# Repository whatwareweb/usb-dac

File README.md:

# usb-dac

USB DAC based on TI PCM2912A IC

This design is tested and working, I use it as my daily driver DAC

## pcb fabrication
I ordered my pcbs from OSHpark, the project link is here for a 1-click order that is already configured and will work well https://oshpark.com/shared_projects/iy0FjLmS

## performance tweaking
This DAC has been designed with good low-frequency response in mind, large output capacitors are used to ensure very low frequencies can be reproduced

To adjust high-frequency response, C4 and C5 can be decreased to allow higher-frequency sounds to make it to the output. Too high of a capacitance for either of these will lead to a muffled sound

C9 and C10 are the output capacitors, the Rubycon model listed in the BOM does very well for the price but they can be swapped out for any higher quality electrolytic capacitor with the same lead spacing. to increase LF response make these a larger value, to decrease make them a smaller value. I just used these as I had like 70 of them spare from another project

## assembly
Check the assembly directory for assembly pictures

This board design is tested and working, but if you would like any help you can open a github issue and I'll try my best (no i will most likely not give you one for free, sorry)

During assembly it is very helpful to open the board view in KiCad to see the component values and the BOM

This board has been designed with easy assembly in mind, there are only 2 SMD parts which you could get assembled for you at a PCB assembly service, the rest of the parts are through-hole and very easy to solder DIY.

## parts
The parts in the BOM can all be purchased at Mouser electronics (DigiKey probably has them too, I didn't check)

I just went with the cheapest option of the rated component value with a minimum voltage rating of 5v, so if you need to get components from some other supplier you can do that as well and it will probably work, just make sure to double-check the lead spacing for the capacitors, inductors, etc

## bom
To export the BOM, open the schematic in Kicad, and click the BOM icon in the toolbar, from there you can copy/paste or export

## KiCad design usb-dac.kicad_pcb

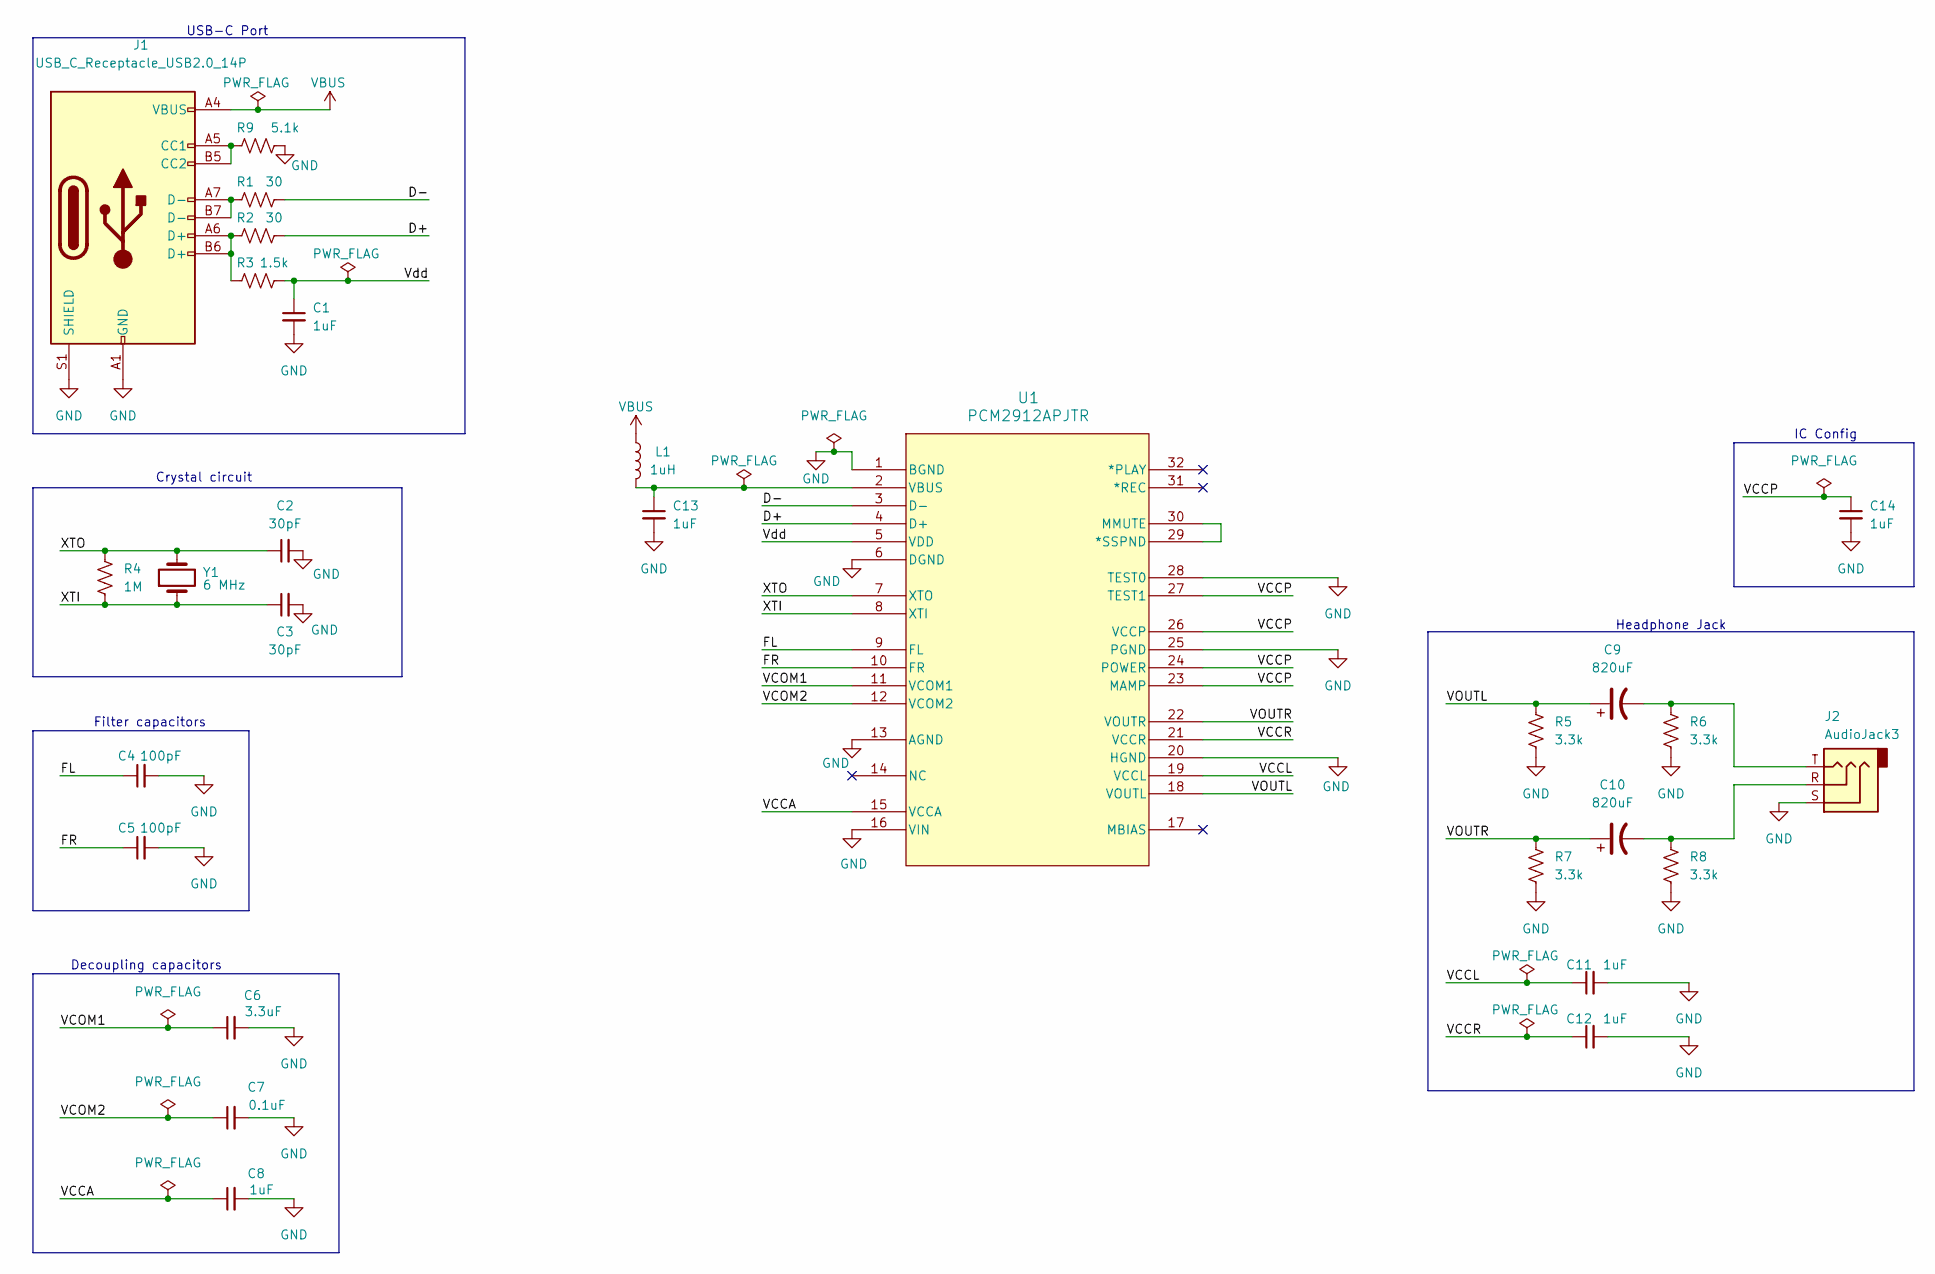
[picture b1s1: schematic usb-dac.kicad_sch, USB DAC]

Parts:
C1, C8, C11, C12, C13, C14: 1uF; C_Rect_L7.0mm_W2.0mm_P5.00mm; Mfr. # FG28X7R1E105KRT00
C2, C3: 30pF; C_Rect_L7.0mm_W2.0mm_P5.00mm; Mfr. # K300J10C0GF5UH5
C4, C5: 100pF; C_Rect_L7.0mm_W2.0mm_P5.00mm; Mfr. # XR501101K040HAND5P
C6: 3.3uF; C_Rect_L7.0mm_W2.0mm_P5.00mm; Mfr. # FA24X7R1E335KRU06
C7: 0.1uF; C_Rect_L7.0mm_W2.0mm_P5.00mm; Mfr. # K104K10X7RF5UH5
C9, C10: 820uF; CP_Radial_D8.0mm_P3.50mm; Mfr. # 6.3ZLH820MEFC8X11.5
J1: USB_C_Receptacle_USB2.0_14P; USB_C_Receptacle_GCT_USB4105-xx-A_16P_TopMnt_Horizontal; Mfr. # USB4085
J2: AudioJack3; Jack_3.5mm_CUI_SJ1-3523N_Horizontal; Mfr. # SJ1-3523N
L1: 1uH; L_Axial_L5.3mm_D2.2mm_P7.62mm_Horizontal_Vishay_IM-1; Mfr. # AICC-02-1R0M-T
R1, R2: 30; R_Axial_DIN0207_L6.3mm_D2.5mm_P10.16mm_Horizontal; Mfr. # CF14JT30R0
R3: 1.5k; R_Axial_DIN0207_L6.3mm_D2.5mm_P10.16mm_Horizontal; Mfr. # CFR-12JB-52-1K5
R4: 1M; R_Axial_DIN0207_L6.3mm_D2.5mm_P10.16mm_Horizontal; Mfr. # RNF18FTD1M00
R5, R6, R7, R8: 3.3k; R_Axial_DIN0207_L6.3mm_D2.5mm_P10.16mm_Horizontal; Mfr. # CFM14JT3K30
R9: 5.1k; R_Axial_DIN0207_L6.3mm_D2.5mm_P10.16mm_Horizontal; Mfr. # CF18JT5K10
U1: PCM2912APJTR; TQFP-32_7x7mm_P0.8mm; Mfr. # PCM2912APJTR
Y1: 6 MHz; Crystal_HC49-U_Vertical; Mfr. # ATS060

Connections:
/D+: R2.2, U1.4 (D+)
/D-: R1.2, U1.3 (D-)
/FL: C4.1, U1.9 (FL)
/FR: C5.1, U1.10 (FR)
/VCCA: C8.1, U1.15 (VCCA)
/VCCL: C11.1, U1.19 (VCCL)
/VCCP: C14.1, U1.23 (MAMP), U1.24 (POWER), U1.26 (VCCP), U1.27 (TEST1)
/VCCR: C12.1, U1.21 (VCCR)
/VCOM1: C6.1, U1.11 (VCOM1)
/VCOM2: C7.1, U1.12 (VCOM2)
/VOUTL: C9.1, R5.1, U1.18 (VOUTL)
/VOUTR: C10.1, R7.1, U1.22 (VOUTR)
/Vdd: C1.1, R3.2, U1.5 (VDD)
/XTI: C3.1, R4.2, U1.8 (XTI), Y1.1
/XTO: C2.1, R4.1, U1.7 (XTO), Y1.2
GND: C1.2, C2.2, C3.2, C4.2, C5.2, C6.2, C7.2, C8.2, C11.2, C12.2, C13.2, C14.2, J1.A1 (GND), J1.A12 (GND), J1.B1 (GND), J1.B12 (GND), J1.S1 (SHIELD), J2.S, R5.2, R6.2, R7.2, R8.2, R9.2, U1.1 (BGND), U1.6 (DGND), U1.13 (AGND), U1.16 (VIN), U1.20 (HGND), U1.25 (PGND), U1.28 (TEST0)
unnamed: C9.2, J2.T, R6.1
unnamed: C10.2, J2.R, R8.1
unnamed: J1.A5 (CC1), J1.B5 (CC2), R9.1
unnamed: J1.A6 (D+), J1.B6 (D+), R2.1, R3.1
unnamed: J1.A7 (D-), J1.B7 (D-), R1.1
unnamed: U1.29 (*SSPND), U1.30 (MMUTE)
unnamed: C13.1, L1.2, U1.2 (VBUS)
VBUS: J1.A4 (VBUS), J1.A9 (VBUS), J1.B4 (VBUS), J1.B9 (VBUS), L1.1

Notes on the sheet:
Filter capacitors
Headphone Jack
USB-C Port
Crystal circuit
Decoupling capacitors
IC Config

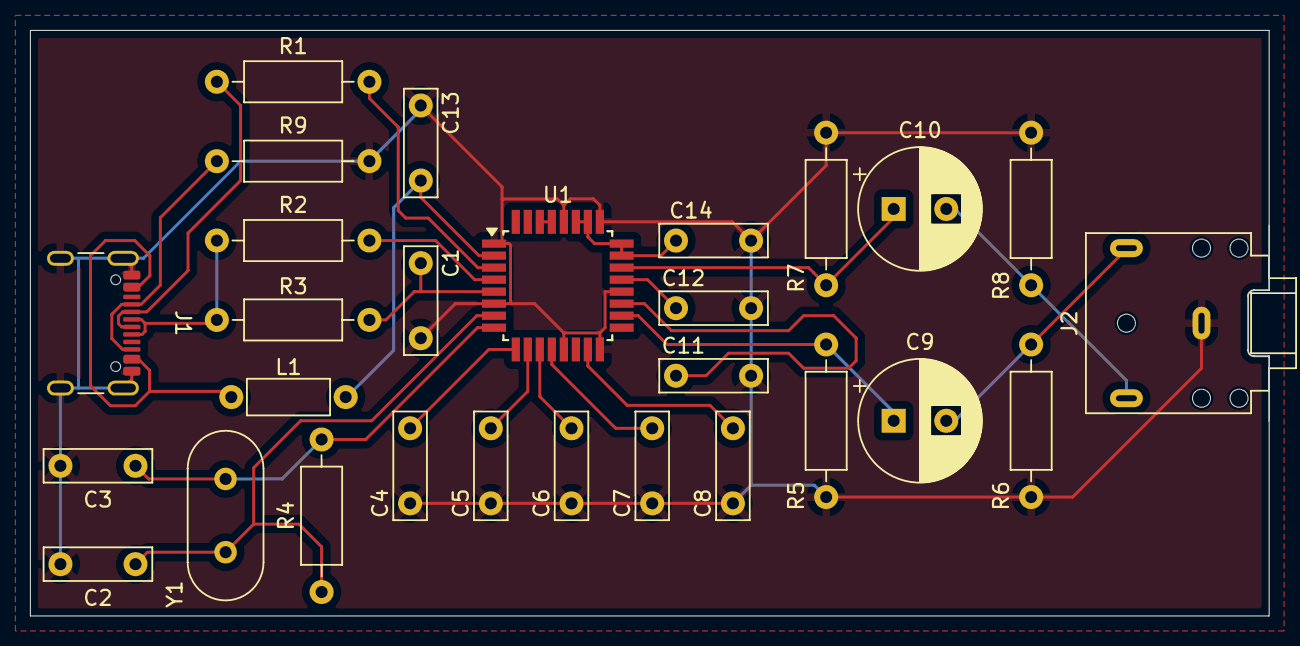
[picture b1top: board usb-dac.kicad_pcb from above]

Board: 2 copper layers, 82.5 x 38.9 mm, 28 parts (0 on the bottom side), 24 nets.

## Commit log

2024-07-12 Add initial libraries and schematics
2024-07-12 Create LICENSE
2024-07-12 Update schematic
2024-07-13 update schematic with new components
2024-07-13 Update schematic with separate chunks for different objects
2024-07-13 Work on schematic
2024-07-14 Some more work on the schematic
2024-07-15 More work on schematic Add headphone jack and reduce error amount
2024-07-15 Finish schematic
2024-07-16 Finished schematic
2024-07-16 Work on PCB
2024-07-17 Add more footprints
2024-07-18 BOM edits and footprint additions
2024-07-18 BOM and footprint work
2024-07-19 Start PCB placements
2024-07-20 Finish PCB and clarify schematic
2024-07-20 Update PCB with new schematic data
2024-07-21 Update some small tweaks
2024-07-21 add "branding"
2024-08-05 correct resistor and type-c port models
2024-08-06 Add a in-stock capacitor part
2024-08-06 add assembly images, SMD parts and resistors
2024-08-07 Add final assembly pictures
2024-08-07 add board2 assembly
2024-08-21 add documentation
2024-08-21 update readme with bom info
2025-01-01 "Professionalize" README.md
